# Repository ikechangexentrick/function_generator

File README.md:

# function_generator
8 channel clock processor/low frequency oscillator

### [Schematic](https://raw.githubusercontent.com/ikechangexentrick/function_generator/master/hw/function_generator_v1_schematic.pdf)

## Prerequisites

### Hardware
- Raspberry Pi Pico
- SSD1306 based OLED display
  - I use [0.96in 128x64 OLED display](https://akizukidenshi.com/catalog/g/gP-12031/)
- MCP4922 Digital-to-Analog converter

### Software (Arduino libraries)
- [Display_OLED](https://github.com/ikechangexentrick/Display_OLED)
  - (required libraries also)
- [AD_DA_Converters](https://github.com/ikechangexentrick/AD_DA_Converters)

## Build instruction

... to be written ...

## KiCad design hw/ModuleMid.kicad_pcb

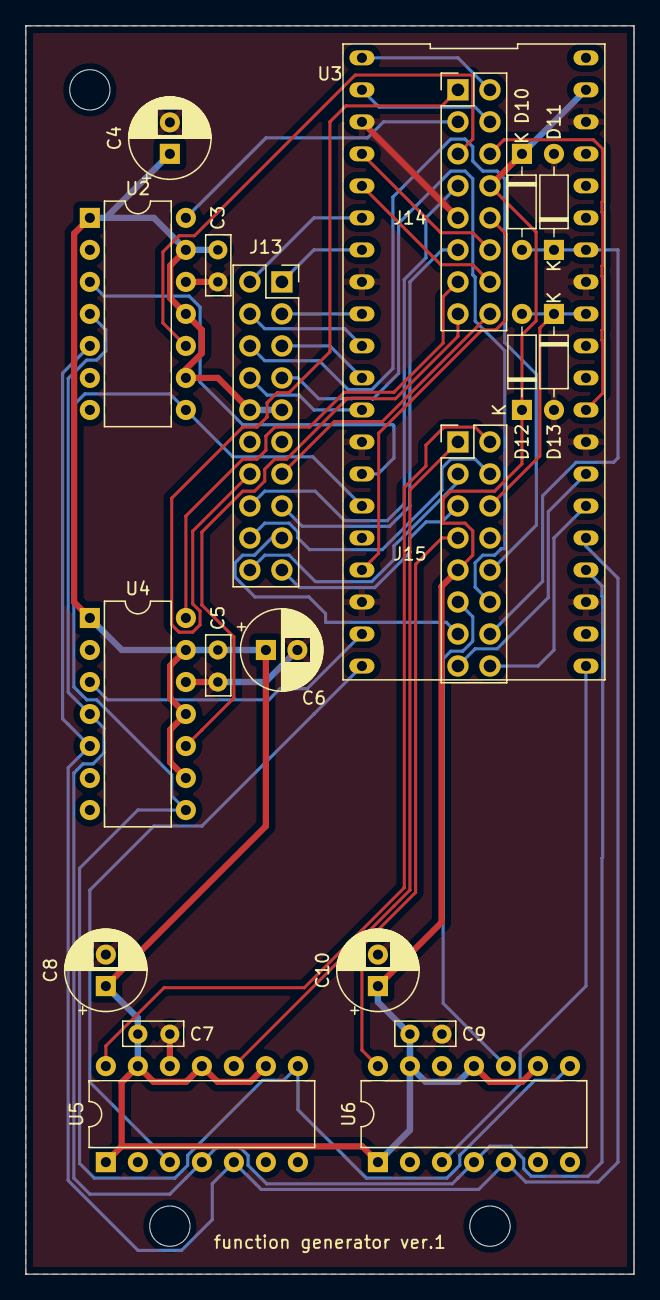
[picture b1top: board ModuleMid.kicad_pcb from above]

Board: 2 copper layers, 48.3 x 99.1 mm, 20 parts (0 on the bottom side), 43 nets.

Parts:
C3, C5, C7, C9: 0.1u; C_Axial_L4.8mm_D2.0mm_P2.54mm_Horizontal
C4, C6, C8, C10: 10u; CP_Radial_D6.3mm_P2.50mm
D10, D11, D12, D13: 1N4148; D_DO-35_SOD27_P7.62mm_Horizontal
J13: interface_to_mid; PinSocket_2x10_P2.54mm_Vertical
J14: mid_to_back_1; PinHeader_2x08_P2.54mm_Vertical
J15: mid_to_back_2; PinHeader_2x08_P2.54mm_Vertical
U2, U4, U5, U6: MCP4922; DIP-14_W7.62mm
U3: RaspberryPi_Pico; Raspberry_Pi_pico_topside_up

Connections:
+3V3: C3.1, C4.1, C5.1, C6.1, C7.1, C8.1, C9.1, C10.1, D10.1, D12.1, J13.9, J13.10, J14.8, J15.9, U2.1, U2.9, U2.11, U2.13, U3.39, U4.1, U4.9, U4.11, U4.13, U5.1, U5.9, U5.11, U5.13, U6.1, U6.9, U6.11, U6.13
/RPi and DACs/RE1: J13.4, U3.10
/RPi and DACs/RE2: J13.3, U3.9
/RPi and DACs/button: J13.5, U3.11
/RPi and DACs/clock: J13.8, U3.12
/RPi and DACs/cv1: D12.2, D13.1, J15.6, U3.32
/RPi and DACs/cv2: D10.2, D11.1, J15.14, U3.34
/RPi and DACs/cv_1_in: J13.6, J15.10
/RPi and DACs/cv_2_in: J13.7, J15.12
/RPi and DACs/da_cs_1: U2.3, U3.14
/RPi and DACs/da_cs_2: U3.19, U4.3
/RPi and DACs/da_cs_3: U3.20, U5.3
/RPi and DACs/da_cs_4: U3.21, U6.3
/RPi and DACs/dac_1_a: J14.3, U2.14
/RPi and DACs/dac_1_b: J14.5, U2.10
/RPi and DACs/dac_2_a: J14.13, U4.14
/RPi and DACs/dac_2_b: J14.15, U4.10
/RPi and DACs/dac_3_a: J15.2, U5.14
/RPi and DACs/dac_3_b: J15.1, U5.10
/RPi and DACs/dac_4_a: J15.7, U6.14
/RPi and DACs/dac_4_b: J15.11, U6.10
/RPi and DACs/display_scl: J13.1, U3.7
/RPi and DACs/display_sda: J13.2, U3.6
/RPi and DACs/latch: U2.8, U3.15, U4.8, U5.8, U6.8
/RPi and DACs/out_1: J13.14, J14.1
/RPi and DACs/out_2: J13.16, J14.7
/RPi and DACs/out_3: J13.15, J14.11
/RPi and DACs/out_4: J13.13, J14.16
/RPi and DACs/out_5: J13.18, J15.4
/RPi and DACs/out_6: J13.20, J15.3
/RPi and DACs/out_7: J13.19, J15.5
/RPi and DACs/out_8: J13.17, J15.13
/RPi and DACs/polarity_1: J14.2, U3.1
/RPi and DACs/polarity_2: J14.4, U3.2
/RPi and DACs/polarity_3: J14.12, U3.4
/RPi and DACs/polarity_4: J14.14, U3.5
/RPi and DACs/polarity_5: J14.6, U3.29
/RPi and DACs/polarity_6: J14.10, U3.17
/RPi and DACs/polarity_7: J15.16, U3.26
/RPi and DACs/polarity_8: J15.15, U3.27
/RPi and DACs/spi_ck: U2.4, U3.24, U4.4, U5.4, U6.4
/RPi and DACs/spi_mosi: U2.5, U3.25, U4.5, U5.5, U6.5
GND: C3.2, C4.2, C5.2, C6.2, C7.2, C8.2, C9.2, C10.2, D11.2, D13.2, J13.11, J13.12, J14.9, J15.8, U2.12, U3.3, U3.8, U3.13, U3.18, U3.23, U3.28, U3.33, U3.38, U4.12, U5.12, U6.12

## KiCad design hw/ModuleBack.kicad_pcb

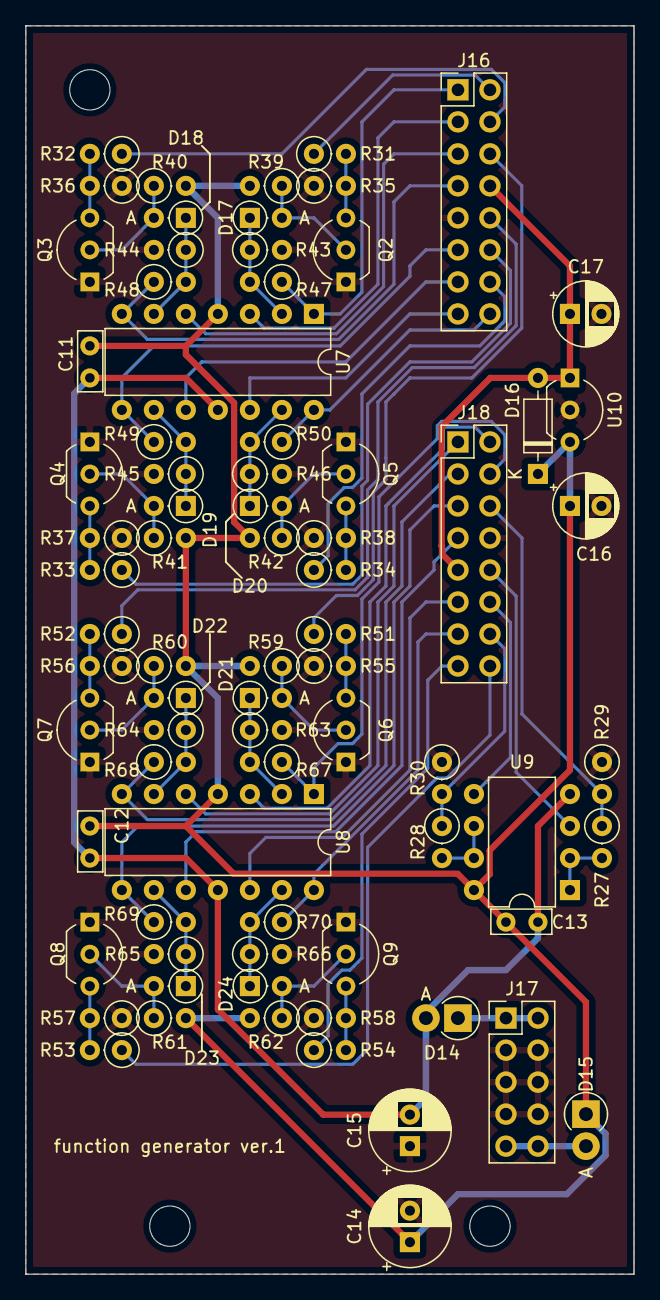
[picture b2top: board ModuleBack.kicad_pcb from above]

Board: 2 copper layers, 48.3 x 99.1 mm, 77 parts (0 on the bottom side), 60 nets.

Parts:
C11, C12, C13: 0.1u; C_Axial_L4.8mm_D2.0mm_P2.54mm_Horizontal
C14, C15: 100u; CP_Radial_D6.3mm_P2.50mm
C16, C17: 10u; CP_Radial_D5.0mm_P2.50mm
D14, D15: 1N5819; D_DO-41_SOD81_P2.54mm_Vertical_AnodeUp
D16: BAT48JFILM; D_DO-35_SOD27_P7.62mm_Horizontal
D17, D18, D19, D20, D21, D22, D23, D24: 1N4148; D_DO-35_SOD27_P2.54mm_Vertical_AnodeUp
J16: mid_to_back_1; PinHeader_2x08_P2.54mm_Vertical
J17: power_bus; PinHeader_2x05_P2.54mm_Vertical
J18: mid_to_back_2; PinHeader_2x08_P2.54mm_Vertical
Q2, Q3, Q4, Q5, Q6, Q7, Q8, Q9: 2SC1815; TO-92_Inline_Wide
R27, R28, R47, R48, R49, R50, R67, R68, R69, R70: 2k; R_Axial_DIN0207_L6.3mm_D2.5mm_P2.54mm_Vertical
R29, R30, R31, R32, R33, R34, R43, R44, R45, R46, R51, R52, R53, R54, R63, R64, R65, R66: 1k; R_Axial_DIN0207_L6.3mm_D2.5mm_P2.54mm_Vertical
R35, R36, R37, R38, R55, R56, R57, R58: 100k; R_Axial_DIN0207_L6.3mm_D2.5mm_P2.54mm_Vertical
R39, R40, R41, R42, R59, R60, R61, R62: 4.7k; R_Axial_DIN0207_L6.3mm_D2.5mm_P2.54mm_Vertical
U7, U8: TL074; DIP-14_W7.62mm
U9: TL072; DIP-8_W7.62mm
U10: LM2950G-3.3; TO-92_Inline_Wide

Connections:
+3V3: C17.1, D16.2, J16.8, J18.9, U10.1
+12V: C11.1, C12.1, C13.1, C14.1, C16.1, D15.1, D16.1, R39.2, R40.2, R41.2, R42.2, R59.2, R60.2, R61.2, R62.2, U7.4, U8.4, U9.8, U10.3
-12V: C11.2, C12.2, C13.2, C15.2, D14.2, U7.11, U8.11, U9.4
/12v_things/cv1: J18.6, R27.1, R29.2
/12v_things/cv2: J18.14, R28.1, R30.2
/12v_things/cv_1_in: J18.10, U9.3
/12v_things/cv_2_in: J18.12, U9.5
/12v_things/dac_1_a: J16.3, U7.3
/12v_things/dac_1_b: J16.5, U7.5
/12v_things/dac_2_a: J16.13, U7.10
/12v_things/dac_2_b: J16.15, U7.12
/12v_things/dac_3_a: J18.2, U8.3
/12v_things/dac_3_b: J18.1, U8.5
/12v_things/dac_4_a: J18.7, U8.10
/12v_things/dac_4_b: J18.11, U8.12
/12v_things/out_1: J16.1, R47.1, U7.1
/12v_things/out_2: J16.7, R48.1, U7.7
/12v_things/out_3: J16.11, R49.1, U7.8
/12v_things/out_4: J16.16, R50.1, U7.14
/12v_things/out_5: J18.4, R67.1, U8.1
/12v_things/out_6: J18.3, R68.1, U8.7
/12v_things/out_7: J18.5, R69.1, U8.8
/12v_things/out_8: J18.13, R70.1, U8.14
/12v_things/polarity_1: J16.2, R31.1
/12v_things/polarity_2: J16.4, R32.1
/12v_things/polarity_3: J16.12, R33.1
/12v_things/polarity_4: J16.14, R34.1
/12v_things/polarity_5: J16.6, R51.1
/12v_things/polarity_6: J16.10, R52.1
/12v_things/polarity_7: J18.16, R53.1
/12v_things/polarity_8: J18.15, R54.1
GND: C14.2, C15.1, C16.2, C17.2, J16.9, J17.3, J17.4, J17.5, J17.6, J17.7, J17.8, J18.8, Q2.1, Q3.1, Q4.1, Q5.1, Q6.1, Q7.1, Q8.1, Q9.1, R29.1, R30.1, R35.1, R36.1, R37.1, R38.1, R43.2, R44.2, R45.2, R46.2, R55.1, R56.1, R57.1, R58.1, R63.2, R64.2, R65.2, R66.2, U10.2
unnamed: D14.1, J17.1, J17.2
unnamed: D15.2, J17.9, J17.10
unnamed: D17.1, R43.1, R47.2, U7.2
unnamed: D17.2, Q2.2, R39.1
unnamed: D18.1, R44.1, R48.2, U7.6
unnamed: D18.2, Q3.2, R40.1
unnamed: D19.1, R45.1, R49.2, U7.9
unnamed: D19.2, Q4.2, R41.1
unnamed: D20.1, R46.1, R50.2, U7.13
unnamed: D20.2, Q5.2, R42.1
unnamed: D21.1, R63.1, R67.2, U8.2
unnamed: D21.2, Q6.2, R59.1
unnamed: D22.1, R64.1, R68.2, U8.6
unnamed: D22.2, Q7.2, R60.1
unnamed: D23.1, R65.1, R69.2, U8.9
unnamed: D23.2, Q8.2, R61.1
unnamed: D24.1, R66.1, R70.2, U8.13
unnamed: D24.2, Q9.2, R62.1
unnamed: Q2.3, R31.2, R35.2
unnamed: Q3.3, R32.2, R36.2
unnamed: Q4.3, R33.2, R37.2
unnamed: Q5.3, R34.2, R38.2
unnamed: Q6.3, R51.2, R55.2
unnamed: Q7.3, R52.2, R56.2
unnamed: Q8.3, R53.2, R57.2
unnamed: Q9.3, R54.2, R58.2
unnamed: R27.2, U9.1, U9.2
unnamed: R28.2, U9.6, U9.7

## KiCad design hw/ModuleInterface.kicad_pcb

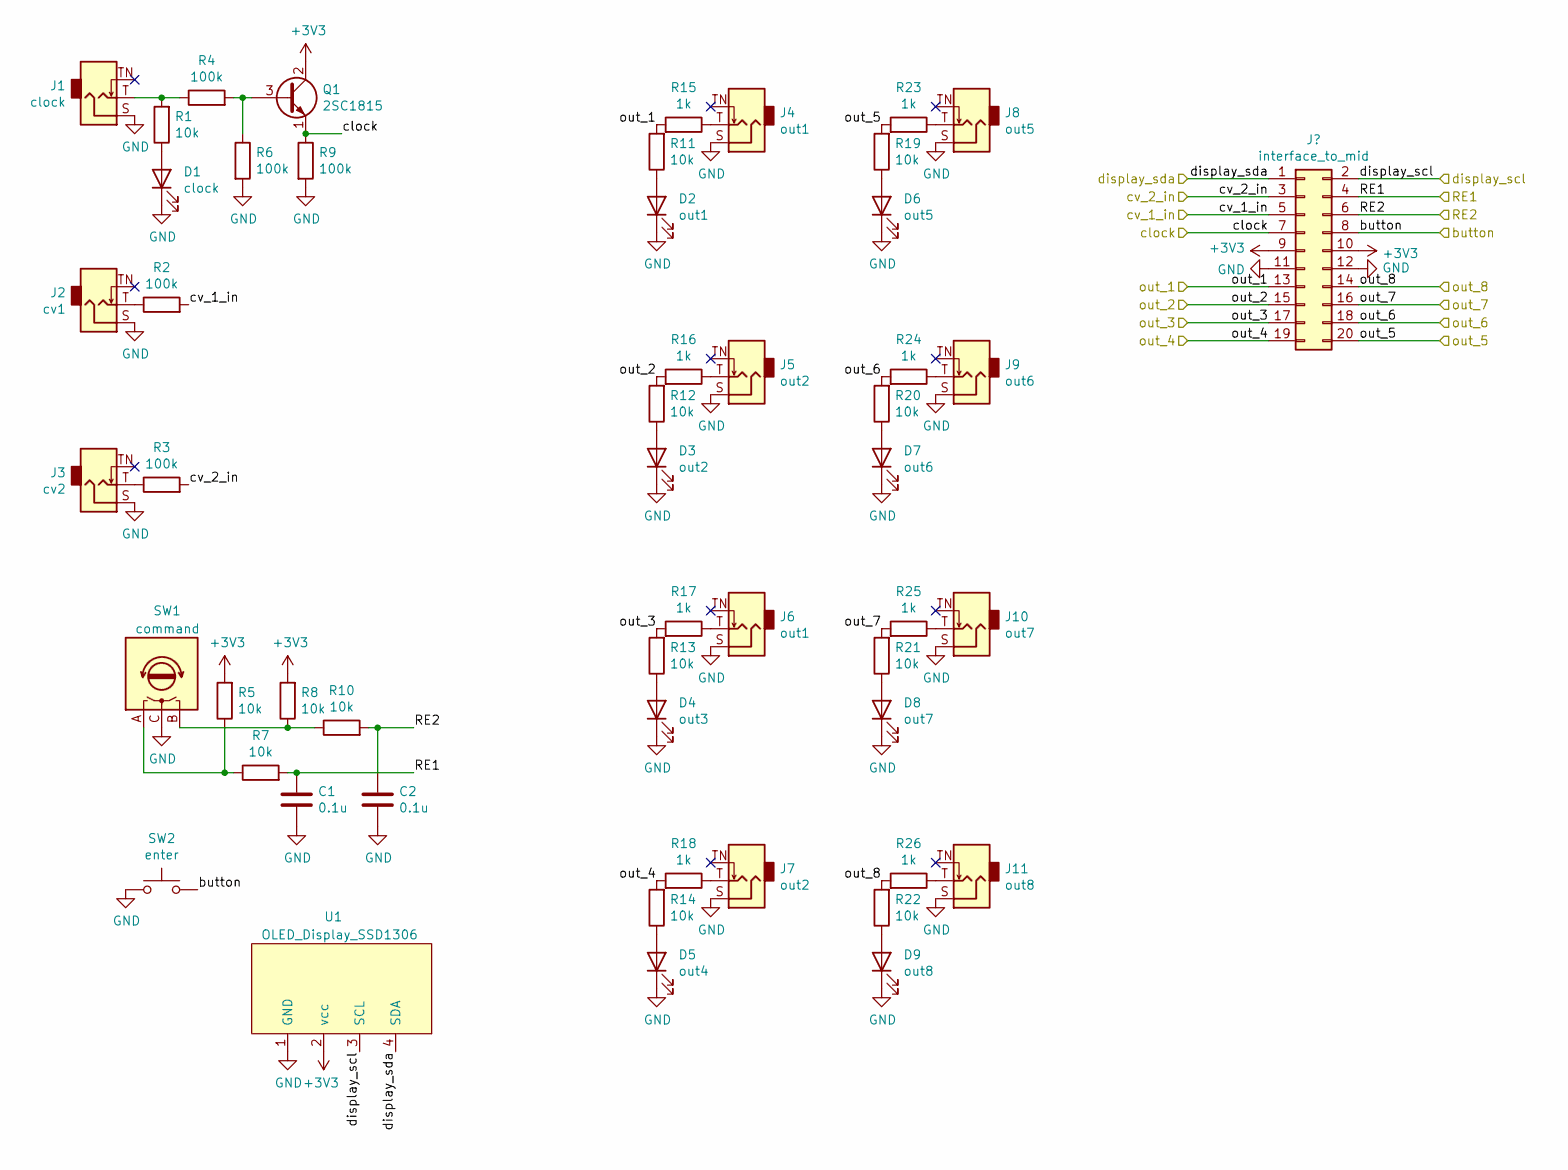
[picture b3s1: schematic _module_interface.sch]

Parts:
C1, C2: 0.1u
D1: clock
D2: out1
D3: out2
D4: out3
D5: out4
D6: out5
D7: out6
D8: out7
D9: out8
J1: clock
J2: cv1
J3: cv2
J4, J6: out1
J5, J7: out2
J8: out5
J9: out6
J10: out7
J11: out8
Q1: 2SC1815; TO-92_Inline
R1, R5, R7, R8, R10, R11, R12, R13, R14, R19, R20, R21, R22: 10k
R2, R3, R4, R6, R9: 100k
R15, R16, R17, R18, R23, R24, R25, R26: 1k
SW1: command
SW2: enter
U1: OLED_Display_SSD1306

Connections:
+3V3: Q1.2 (C), R5.2, R8.2, U1.2 (vcc); also elsewhere on the board
/Interface/RE1: C1.1, R7.2; also elsewhere on the board
/Interface/RE2: C2.1, R10.2; also elsewhere on the board
/Interface/button: SW2.2; also elsewhere on the board
/Interface/clock: Q1.1 (E), R9.1; also elsewhere on the board
/Interface/cv_1_in: R2.2; also elsewhere on the board
/Interface/cv_2_in: R3.2; also elsewhere on the board
/Interface/display_scl: U1.3 (SCL); also elsewhere on the board
/Interface/display_sda: U1.4 (SDA); also elsewhere on the board
/Interface/out_1: R11.2, R15.2; also elsewhere on the board
/Interface/out_2: R12.2, R16.2; also elsewhere on the board
/Interface/out_3: R13.2, R17.2; also elsewhere on the board
/Interface/out_4: R14.2, R18.2; also elsewhere on the board
/Interface/out_5: R19.2, R23.2; also elsewhere on the board
/Interface/out_6: R20.2, R24.2; also elsewhere on the board
/Interface/out_7: R21.2, R25.2; also elsewhere on the board
/Interface/out_8: R22.2, R26.2; also elsewhere on the board
GND: C1.2, C2.2, D1.1 (K), D2.1 (K), D3.1 (K), D4.1 (K), D5.1 (K), D6.1 (K), D7.1 (K), D8.1 (K), D9.1 (K), J1.S, J2.S, J3.S, J4.S, J5.S, J6.S, J7.S, J8.S, J9.S, J10.S, J11.S, R6.2, R9.2, SW1.C, SW2.1, U1.1 (GND); also elsewhere on the board
unnamed: D1.2 (A), R1.1
unnamed: D2.2 (A), R11.1
unnamed: D3.2 (A), R12.1
unnamed: D4.2 (A), R13.1
unnamed: D5.2 (A), R14.1
unnamed: D6.2 (A), R19.1
unnamed: D7.2 (A), R20.1
unnamed: D8.2 (A), R21.1
unnamed: D9.2 (A), R22.1
unnamed: J1.T, R1.2, R4.1
unnamed: J2.T, R2.1
unnamed: J3.T, R3.1
unnamed: J4.T, R15.1
unnamed: J5.T, R16.1
unnamed: J6.T, R17.1
unnamed: J7.T, R18.1
unnamed: J8.T, R23.1
unnamed: J9.T, R24.1
unnamed: J10.T, R25.1
unnamed: J11.T, R26.1
unnamed: Q1.3 (B), R4.2, R6.1
unnamed: R5.1, R7.1, SW1.A
unnamed: R8.1, R10.1, SW1.B

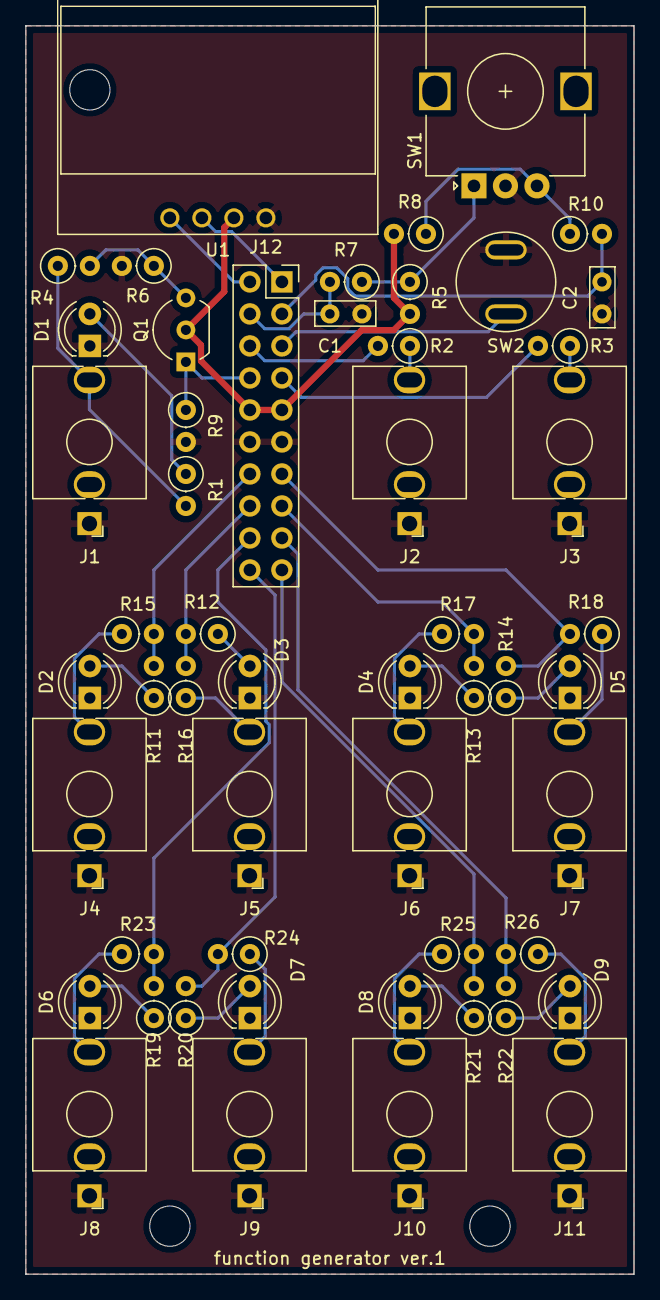
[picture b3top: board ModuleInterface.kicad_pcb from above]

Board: 2 copper layers, 48.3 x 99.1 mm, 53 parts (0 on the bottom side), 41 nets.

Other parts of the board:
J12: interface_to_mid; PinSocket_2x10_P2.54mm_Vertical

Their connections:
+3V3: J12.9, J12.10; also elsewhere on the board
/Interface/RE1: J12.4; also elsewhere on the board
/Interface/RE2: J12.3; also elsewhere on the board
/Interface/button: J12.5; also elsewhere on the board
/Interface/clock: J12.8; also elsewhere on the board
/Interface/cv_1_in: J12.6; also elsewhere on the board
/Interface/cv_2_in: J12.7; also elsewhere on the board
/Interface/display_scl: J12.1; also elsewhere on the board
/Interface/display_sda: J12.2; also elsewhere on the board
/Interface/out_1: J12.14; also elsewhere on the board
/Interface/out_2: J12.16; also elsewhere on the board
/Interface/out_3: J12.15; also elsewhere on the board
/Interface/out_4: J12.13; also elsewhere on the board
/Interface/out_5: J12.18; also elsewhere on the board
/Interface/out_6: J12.20; also elsewhere on the board
/Interface/out_7: J12.19; also elsewhere on the board
/Interface/out_8: J12.17; also elsewhere on the board
GND: J12.11, J12.12; also elsewhere on the board

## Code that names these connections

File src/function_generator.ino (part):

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*/

const int PIN_DA_CS = 10;
const int PIN_DA_CS_2 = 12;
const int PIN_DA_CS_3 = 13;
const int PIN_DA_CS_4 = 14;

const int PIN_DA_LATCH = 11;

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//  -----------------------------------------------

MCP4922 dac1(settings, PIN_DA_CS, PIN_DA_LATCH);
MCP4922 dac2(settings, PIN_DA_CS_2, PIN_DA_LATCH);
MCP4922 dac3(settings, PIN_DA_CS_3, PIN_DA_LATCH);
MCP4922 dac4(settings, PIN_DA_CS_4, PIN_DA_LATCH);

//  -----------------------------------------------

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	randomSeed(analogRead(PIN_RANDOM_SEED));

	pinMode(PIN_DA_CS, OUTPUT);
	pinMode(PIN_DA_CS_2, OUTPUT);
	pinMode(PIN_DA_CS_3, OUTPUT);
	pinMode(PIN_DA_CS_4, OUTPUT);
	pinMode(PIN_DA_LATCH, OUTPUT);

	pinMode(PIN_ROTARY_SW1, INPUT);
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
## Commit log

2022-06-20 Software: supports 8 channel output. supports CV control functionality.
    Hardware:
    appended kicad project files.
2022-06-20 Master channel for synchronization can be selected via "Source" menu. Improved phase stability of synchronization. "onPeriodStarts" callback will be called when a period starts for each channel.
2022-06-20 Multi channel support. Note that currently only 2 outputs are hard-coded.
2022-06-20 low-frequency function generator, on Raspberry Pi Pico.
2022-06-20 Updated menu structure; different representation for "switch" and "sub menu" types. Added AR (Attack-Release) envelope function. Added "Pattern" functionality; supports euclidean rhythm. Fixed a bug 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
2022-06-20 Followed Display_OLED's update.
2022-06-20 Software: appended polarity selection functionality. Hardware: appended power reversal protection. adjusted silks.
2022-06-20 hardware: artwork done.
2022-09-08 Software: - Added CV control, but for limited functions. - Added BPM mode.
    Hardware:
    - Version ordered to Elecrow.
2022-09-08 corrected README.md's position.
2022-09-27 Implemented CV functions had been left. Adjusted initial settings.
2022-09-30 Improved the usability of CV config menu.
2022-09-30 branch for images on README.md
2022-09-30 Added schematic pdf.
